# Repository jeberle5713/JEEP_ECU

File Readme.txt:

See TractorEnvy.Com for project description.

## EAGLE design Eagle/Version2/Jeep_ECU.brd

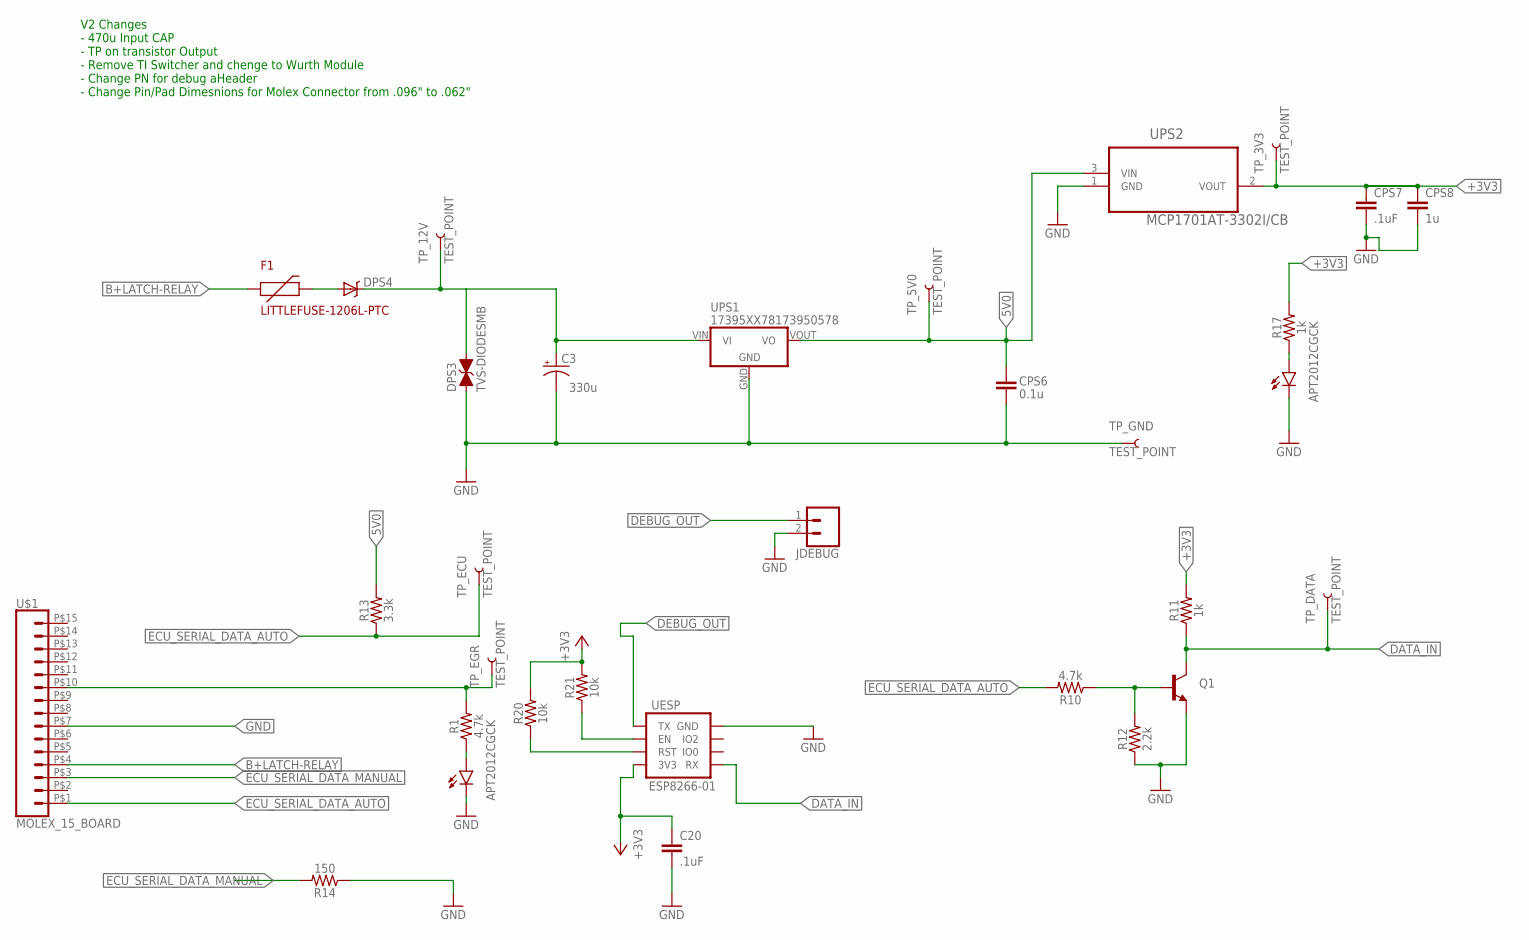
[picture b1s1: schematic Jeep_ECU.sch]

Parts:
C3: 330u; 8X10MM-ELECTROLYTIC
C20: .1uF; 0603-CAP
CPS6: 0.1u; 0603-CAP
CPS7: .1uF; 0603-CAP
CPS8: 1u; 0603-CAP
DPS3: TVS-DIODESMB; SMB-DIODE
DPS4: SCHOTTKY-DIODESSOD123SOD; SOD-123F
F1: LITTLEFUSE-1206L-PTC; 1206
JDEBUG: CONN_02; 1X02
LED_EGR: APT2012CGCK; 0805-LED
LED_PWR: APT2012CGCK; 0805-LED
Q1: NPN-TRANSISTORMMBT3904-SOT23; SOT23
R1, R10: 4.7k; 0603
R11, R17: 1k; 0603
R12: 2.2k; 0603
R13: 3.3k; 0603
R14: 150; 0603
R20, R21: 10k; 0603
TP_3V3, TP_5V0, TP_12V: TEST_POINT
TP_DATA: TEST_POINT
TP_ECU: TEST_POINT
TP_EGR: TEST_POINT
TP_GND: TEST_POINT
U$1: MOLEX_15_BOARD; MOLEX_15PIN_BOARD
UESP: ESP8266-01
UPS1: 17395XX78173950578; 17395XX78
UPS2: MCP1701AT-3302I/CB; SOT95P255X145-3N

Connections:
5V0: CPS6.1, R13.2, TP_5V0.P$1, UPS1.VOUT (VO), UPS2.3 (VIN)
+3V3: C20.1, CPS7.1, CPS8.1, R11.2, R17.2, R20.2, R21.2, TP_3V3.P$1, UESP.2 (3V3), UPS2.2 (VOUT)
B+LATCH-RELAY: F1.1 (P$1+), U$1.P$4 (4)
DATA_IN: Q1.3 (C), R11.1, TP_DATA.P$1, UESP.1 (RX)
DEBUG_OUT: JDEBUG.1, UESP.8 (TX)
ECU_SERIAL_DATA_AUTO: R10.2, R13.1, TP_ECU.P$1, U$1.P$1 (1)
ECU_SERIAL_DATA_MANUAL: R14.2, U$1.P$3 (3)
GND: C3.-, C20.2, CPS6.2, CPS7.2, CPS8.2, DPS3.A, JDEBUG.2, LED_EGR.C, LED_PWR.C, Q1.2 (E), R12.1, R14.1, TP_GND.P$1, U$1.P$7 (7), UESP.7 (GND), UPS1.GND (GND/ADJ), UPS2.1 (GND)
unnamed: R1.2, TP_EGR.P$1, U$1.P$10 (10)
unnamed: DPS4.A, F1.2 (P$2-)
unnamed: R20.1, UESP.4 (RST)
unnamed: R21.1, UESP.6 (EN)
unnamed: LED_EGR.A, R1.1
unnamed: Q1.1 (B), R10.1, R12.2
unnamed: LED_PWR.A, R17.1
VBR: C3.+, DPS3.C, DPS4.C, TP_12V.P$1, UPS1.VIN (VI)

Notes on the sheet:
V2 Changes - 470u Input CAP - TP on transistor Output - Remove TI Switcher and chenge to Wurth Module - Change PN for debug aHeader - Change Pin/Pad Dimesnions for Molex Connector from .096" to .062"

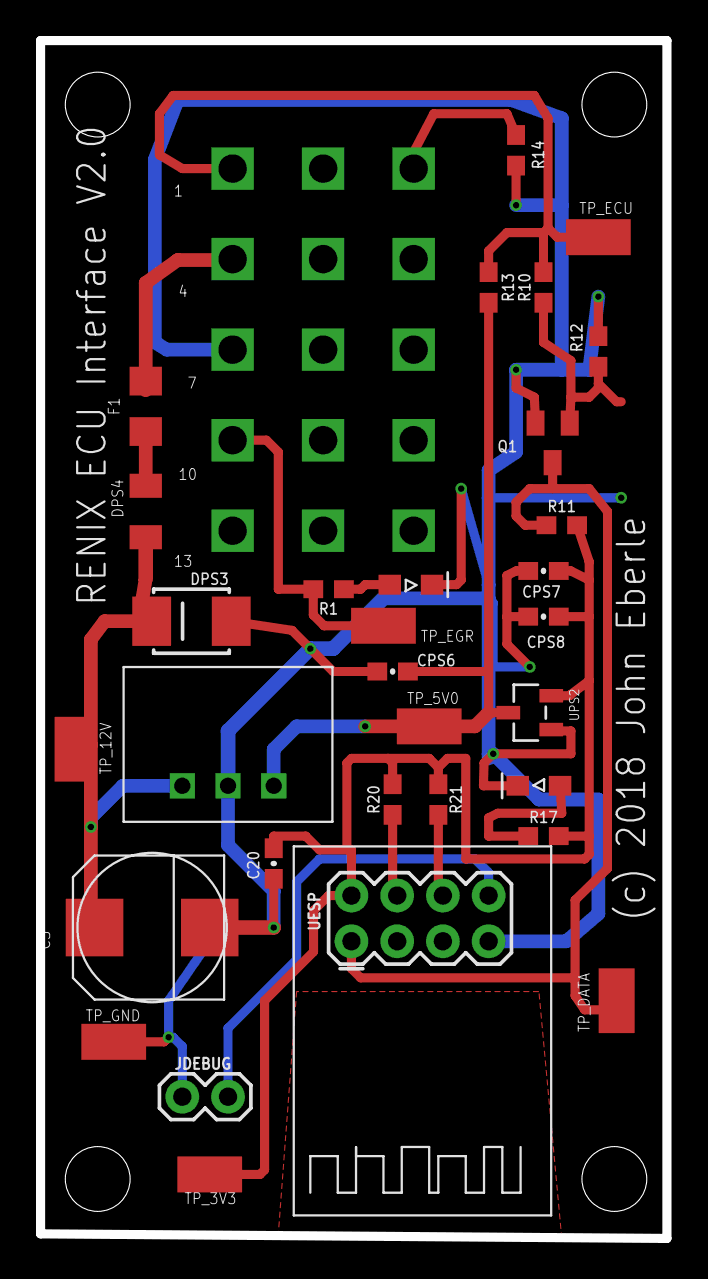
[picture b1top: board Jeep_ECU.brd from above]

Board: 2 copper layers, 34.8 x 66.5 mm, 32 parts (0 on the bottom side), 16 nets.

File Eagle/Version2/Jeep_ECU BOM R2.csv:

Part;Value;PN;VDC;
R14;150;ERJ-3GEYJ151V;;ok
R20; 10k;ERJ-3GEYJ103V;;ok
R21; 10k;ERJ-3GEYJ103V;;ok
R11; 1k;ERJ-3GEYJ102V;;ok
R17; 1k;ERJ-3GEYJ102V;;ok
R12; 2.2k;ERJ-3GEYJ222V;;ok
R13; 3.3k;ERJ-3GEYJ332V;;ok
R10; 4.7k;ERJ-3GEYJ472V;;ok
C20;.1uF;VJ0603Y104JXJCW1BC;16;ok
CPS7;.1uF;VJ0603Y104JXJCW1BC;16;ok
CPS6;0.1u;VJ0603Y104JXJCW1BC;16;ok
U$2;17395XX78173950578;;;ok
CPS8;1u;C0603C105K4RACTU;16;ok
C3;330u;UCL1E331MNL1GS;;
R1;4.7k;ERJ-3GEYJ472V;;ok
LED_EGR;APT2012CGCK;APT2012CGCK;;ok
LED_PWR;APT2012CGCK;APT2012CGCK;;ok
UESP;ESP8266-01;929852-01-04-RB;;ok
F1;LITTLEFUSE-1206L-PTC;1206L025YR;;ok
UPS2;MCP1701AT-3302I/CB;MCP1701AT-3302I/CB;;ok
U$1;MOLEX_15_BOARD;;;ok
Q1;NPN-TRANSISTORMMBT3904-SOT23;MMBT3904LT1G;;ok
DPS4;SCHOTTKY-DIODESSOD123SOD;SS24FL;;ok
TP_3V3;TEST_POINT;S1751-46;;ok
TP_5V0;TEST_POINT;S1751-46;;ok
TP_12V;TEST_POINT;S1751-46;;ok
TP_DATA;TEST_POINT;S1751-46;;ok
TP_ECU;TEST_POINT;S1751-46;;ok
TP_EGR;TEST_POINT;S1751-46;;ok
TP_GND;TEST_POINT;S1751-46;;ok
DPS3;TVS-DIODESMB;SZP6SMB43CAT3G;;ok
JDEBUG;;929870-01-02-RA;;

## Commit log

2018-02-07 Initial Commit.
2018-02-07 Updated BOM
2018-02-07 Added Readme

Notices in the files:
Eagle/Version2/Jeep_ECU.brd:
(c) 2018 John Eberle
parts and their libraries:
SparkFun-Resistors: Licensing: CC v3.0 Share-Alike You are welcome to use this library for commercial purposes.
SparkFun-Connectors: Licensing: Creative Commons ShareAlike 4.0 International - https://creativecommons.org/licenses/by-sa/4.0
